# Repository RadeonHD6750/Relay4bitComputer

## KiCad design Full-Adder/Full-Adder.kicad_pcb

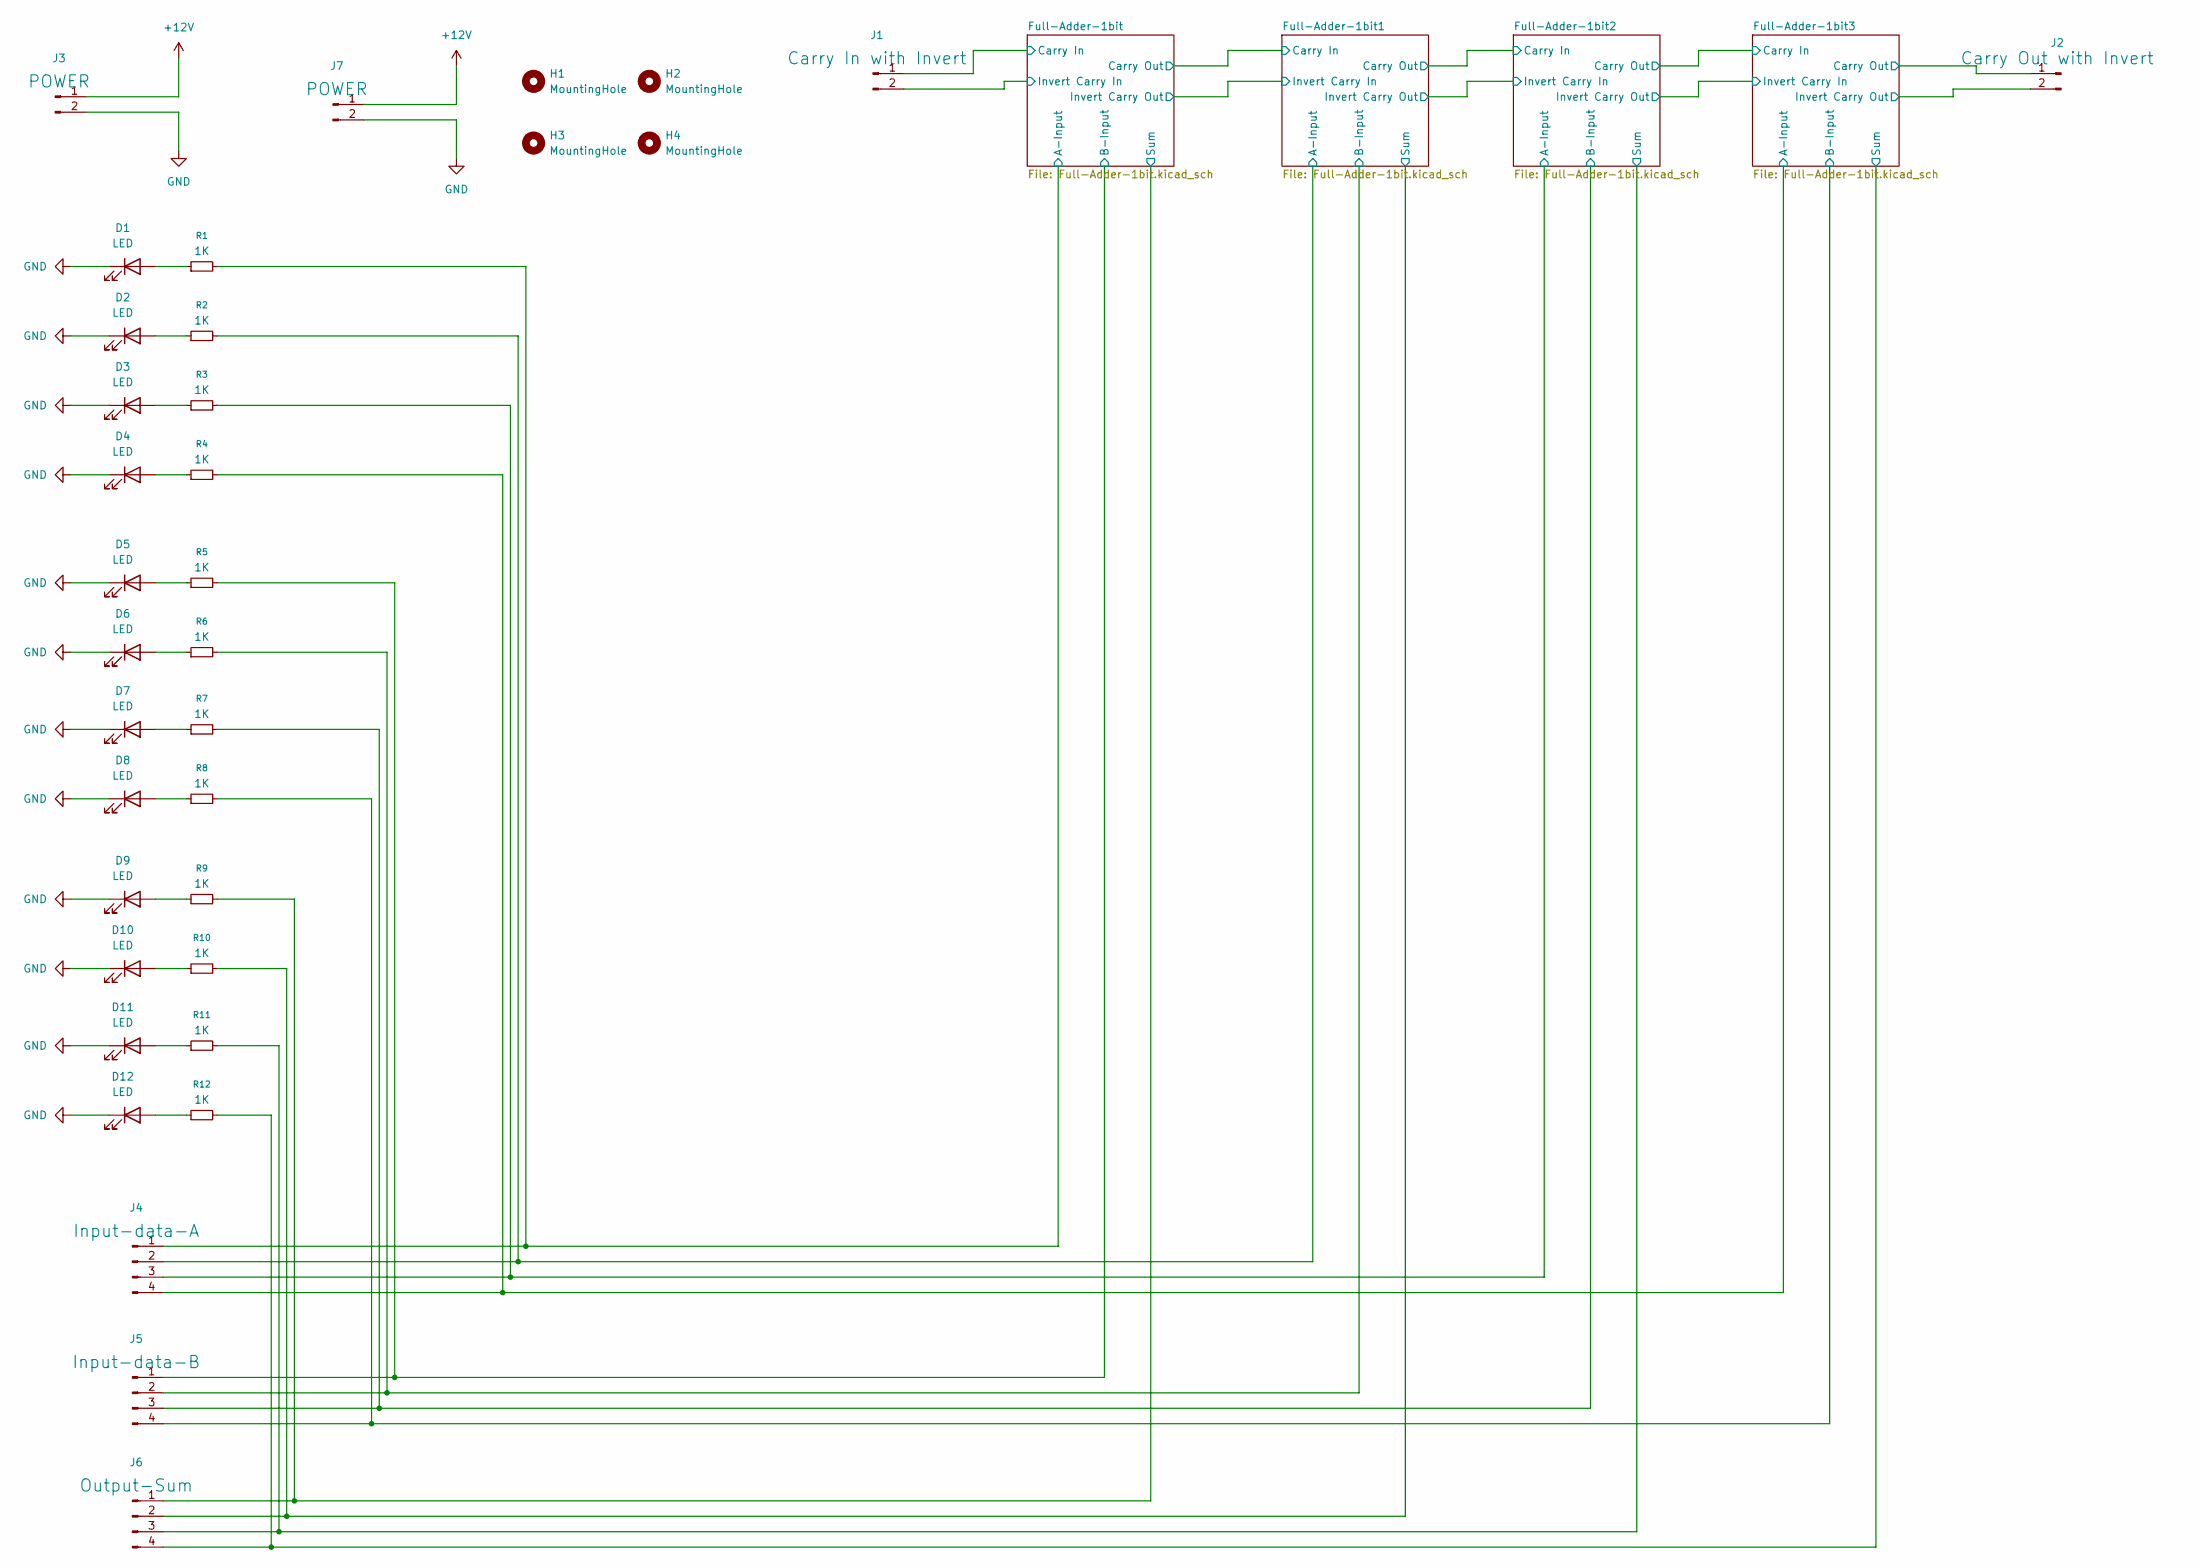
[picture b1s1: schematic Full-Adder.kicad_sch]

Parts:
D1, D2, D3, D4, D5, D6, D7, D8, D9, D10, D11, D12: LED; LED_D5.0mm
H1, H2, H3, H4: MountingHole; MountingHole_3.2mm_M3_Pad
J1: Carry In with Invert; PinHeader_1x02_P2.54mm_Vertical
J2: Carry Out with Invert; PinHeader_1x02_P2.54mm_Vertical
J3, J7: POWER; PinHeader_1x02_P2.54mm_Vertical
J4: Input-data-A; PinHeader_1x04_P2.54mm_Vertical
J5: Input-data-B; PinHeader_1x04_P2.54mm_Vertical
J6: Output-Sum; PinHeader_1x04_P2.54mm_Vertical
R1, R2, R3, R4, R5, R6, R7, R8, R9, R10, R11, R12: 1K; R_Axial_DIN0207_L6.3mm_D2.5mm_P10.16mm_Horizontal

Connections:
+12V: J3.1, J7.1; also elsewhere on the board
/Full-Adder-1bit1/A-Input: J4.2, R2.2; also elsewhere on the board
/Full-Adder-1bit1/B-Input: J5.2, R6.2; also elsewhere on the board
/Full-Adder-1bit1/Sum: J6.2, R10.2; also elsewhere on the board
/Full-Adder-1bit2/A-Input: J4.3, R3.2; also elsewhere on the board
/Full-Adder-1bit2/B-Input: J5.3, R7.2; also elsewhere on the board
/Full-Adder-1bit2/Sum: J6.3, R11.2; also elsewhere on the board
/Full-Adder-1bit3/A-Input: J4.4, R4.2; also elsewhere on the board
/Full-Adder-1bit3/B-Input: J5.4, R8.2; also elsewhere on the board
/Full-Adder-1bit3/Carry Out: J2.1; also elsewhere on the board
/Full-Adder-1bit3/Invert Carry Out: J2.2; also elsewhere on the board
/Full-Adder-1bit3/Sum: J6.4, R12.2; also elsewhere on the board
/Full-Adder-1bit/A-Input: J4.1, R1.2; also elsewhere on the board
/Full-Adder-1bit/B-Input: J5.1, R5.2; also elsewhere on the board
/Full-Adder-1bit/Carry In: J1.1; also elsewhere on the board
/Full-Adder-1bit/Invert Carry In: J1.2; also elsewhere on the board
/Full-Adder-1bit/Sum: J6.1, R9.2; also elsewhere on the board
GND: D1.1 (K), D2.1 (K), D3.1 (K), D4.1 (K), D5.1 (K), D6.1 (K), D7.1 (K), D8.1 (K), D9.1 (K), D10.1 (K), D11.1 (K), D12.1 (K), J3.2, J7.2; also elsewhere on the board
unnamed: D1.2 (A), R1.1
unnamed: D2.2 (A), R2.1
unnamed: D3.2 (A), R3.1
unnamed: D4.2 (A), R4.1
unnamed: D5.2 (A), R5.1
unnamed: D6.2 (A), R6.1
unnamed: D7.2 (A), R7.1
unnamed: D8.2 (A), R8.1
unnamed: D9.2 (A), R9.1
unnamed: D10.2 (A), R10.1
unnamed: D11.2 (A), R11.1
unnamed: D12.2 (A), R12.1

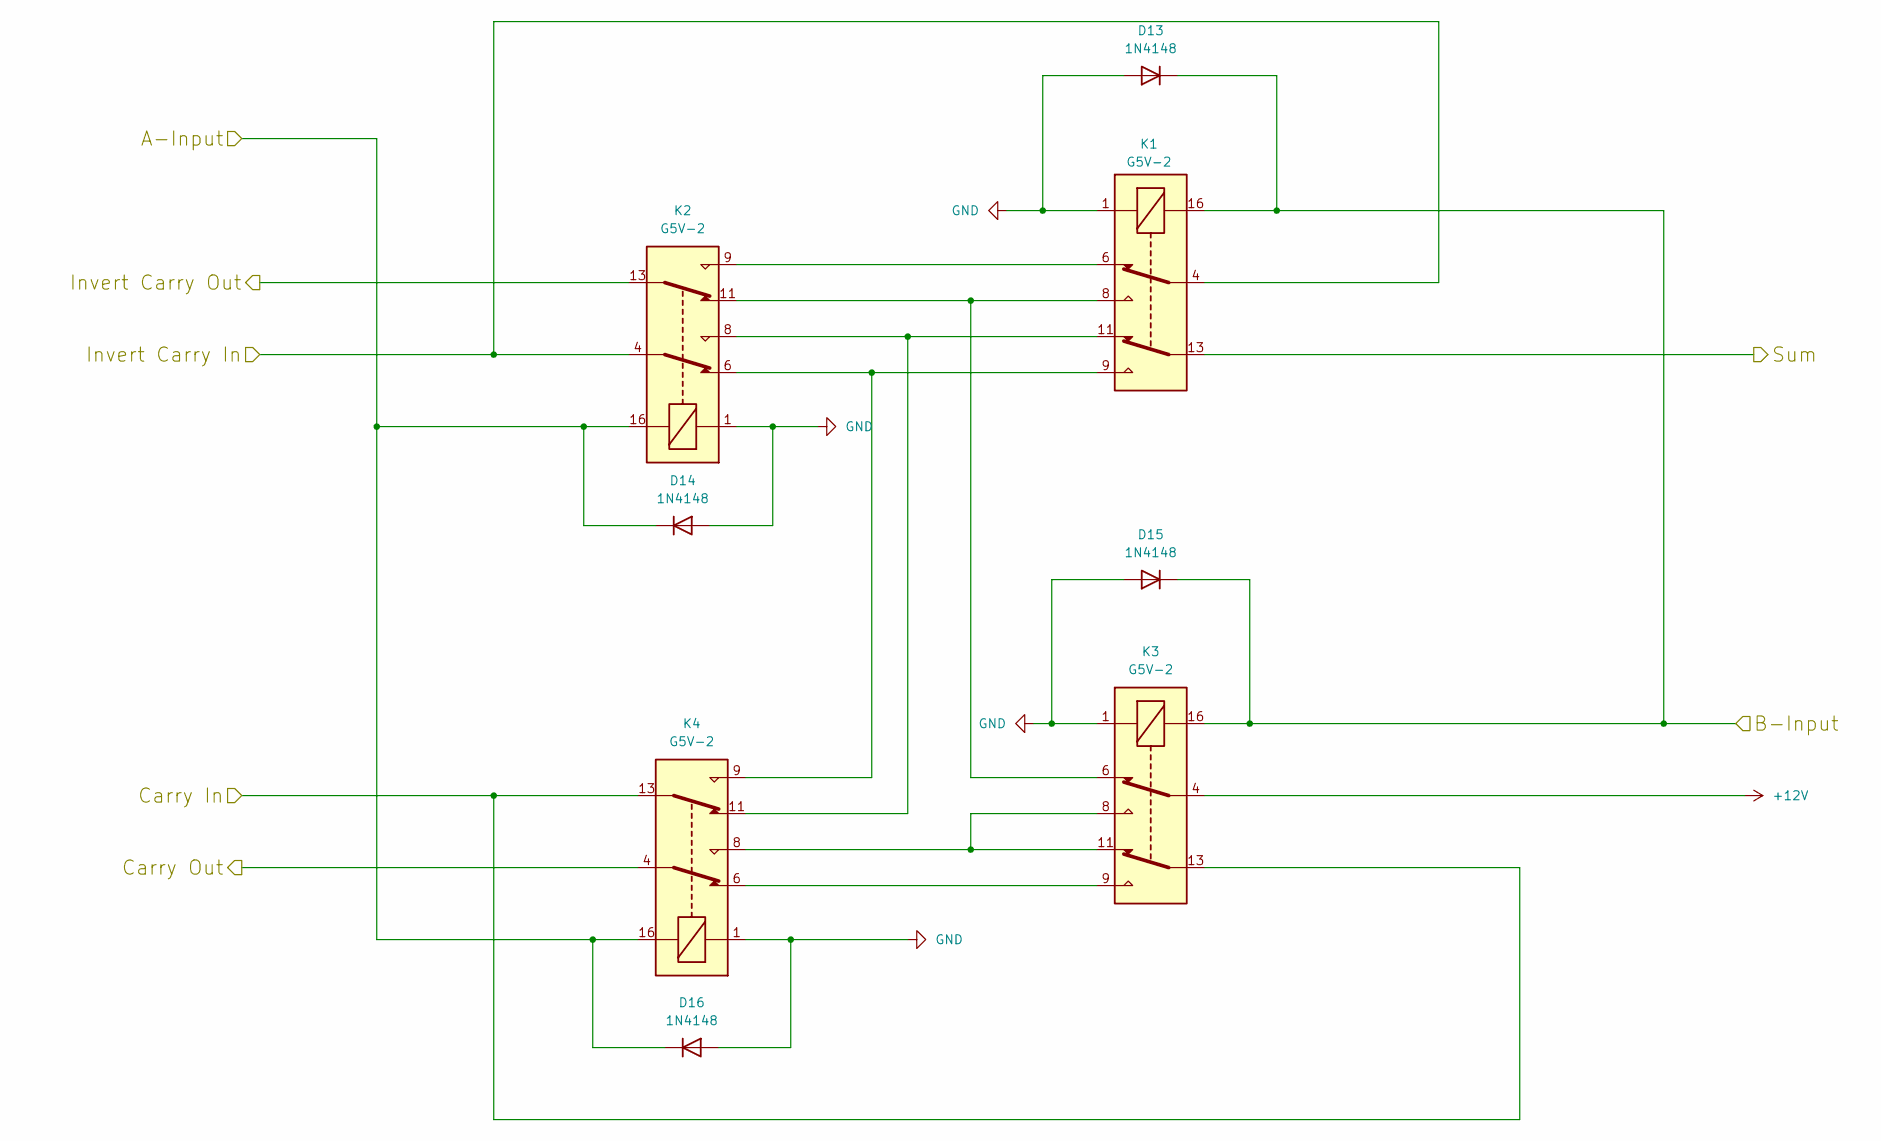
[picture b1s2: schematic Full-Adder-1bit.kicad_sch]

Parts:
D13, D14, D15, D16: 1N4148; D_DO-35_SOD27_P7.62mm_Horizontal
K1, K2, K3, K4: G5V-2; Relay_DPDT_Omron_G5V-2

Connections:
+12V: K3.4; also elsewhere on the board
/Full-Adder-1bit/A-Input: D14.1 (K), D16.1 (K), K2.16, K4.16; also elsewhere on the board
/Full-Adder-1bit/B-Input: D13.1 (K), D15.1 (K), K1.16, K3.16; also elsewhere on the board
/Full-Adder-1bit/Carry In: K3.13, K4.13; also elsewhere on the board
/Full-Adder-1bit/Carry Out: K4.4; also elsewhere on the board
/Full-Adder-1bit/Invert Carry In: K1.4, K2.4; also elsewhere on the board
/Full-Adder-1bit/Invert Carry Out: K2.13; also elsewhere on the board
/Full-Adder-1bit/Sum: K1.13; also elsewhere on the board
GND: D13.2 (A), D14.2 (A), D15.2 (A), D16.2 (A), K1.1, K2.1, K3.1, K4.1; also elsewhere on the board
unnamed: K1.6, K2.9
unnamed: K1.8, K2.11, K3.6
unnamed: K1.9, K2.6, K4.9
unnamed: K1.11, K2.8, K4.11
unnamed: K3.9, K4.6
unnamed: K3.8, K3.11, K4.8

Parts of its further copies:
D17, D18, D19, D20, D21, D22, D23, D24, D25, D26, D27, D28: 1N4148; D_DO-35_SOD27_P7.62mm_Horizontal
K5, K6, K7, K8, K9, K10, K11, K12, K13, K14, K15, K16: G5V-2; Relay_DPDT_Omron_G5V-2

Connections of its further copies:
+12V: K7.4, K11.4, K15.4; also elsewhere on the board
/Full-Adder-1bit1/A-Input: D18.1 (K), D20.1 (K), K6.16, K8.16; also elsewhere on the board
/Full-Adder-1bit1/B-Input: D17.1 (K), D19.1 (K), K5.16, K7.16; also elsewhere on the board
/Full-Adder-1bit1/Carry Out: K8.4, K11.13, K12.13
/Full-Adder-1bit1/Invert Carry Out: K6.13, K9.4, K10.4
/Full-Adder-1bit1/Sum: K5.13; also elsewhere on the board
/Full-Adder-1bit2/A-Input: D22.1 (K), D24.1 (K), K10.16, K12.16; also elsewhere on the board
/Full-Adder-1bit2/B-Input: D21.1 (K), D23.1 (K), K9.16, K11.16; also elsewhere on the board
/Full-Adder-1bit2/Carry Out: K12.4, K15.13, K16.13
/Full-Adder-1bit2/Invert Carry Out: K10.13, K13.4, K14.4
/Full-Adder-1bit2/Sum: K9.13; also elsewhere on the board
/Full-Adder-1bit3/A-Input: D26.1 (K), D28.1 (K), K14.16, K16.16; also elsewhere on the board
/Full-Adder-1bit3/B-Input: D25.1 (K), D27.1 (K), K13.16, K15.16; also elsewhere on the board
/Full-Adder-1bit3/Carry Out: K16.4; also elsewhere on the board
/Full-Adder-1bit3/Invert Carry Out: K14.13; also elsewhere on the board
/Full-Adder-1bit3/Sum: K13.13; also elsewhere on the board
/Full-Adder-1bit/Carry Out: K7.13, K8.13; also elsewhere on the board
/Full-Adder-1bit/Invert Carry Out: K5.4, K6.4; also elsewhere on the board
GND: D17.2 (A), D18.2 (A), D19.2 (A), D20.2 (A), D21.2 (A), D22.2 (A), D23.2 (A), D24.2 (A), D25.2 (A), D26.2 (A), D27.2 (A), D28.2 (A), K5.1, K6.1, K7.1, K8.1, K9.1, K10.1, K11.1, K12.1, K13.1, K14.1, K15.1, K16.1; also elsewhere on the board
unnamed: K5.6, K6.9
unnamed: K5.8, K6.11, K7.6
unnamed: K5.9, K6.6, K8.9
unnamed: K5.11, K6.8, K8.11
unnamed: K7.9, K8.6
unnamed: K7.8, K7.11, K8.8
unnamed: K9.9, K10.6, K12.9
unnamed: K9.11, K10.8, K12.11
unnamed: K9.6, K10.9
unnamed: K9.8, K10.11, K11.6
unnamed: K11.9, K12.6
unnamed: K11.8, K11.11, K12.8
unnamed: K13.6, K14.9
unnamed: K13.8, K14.11, K15.6
unnamed: K13.9, K14.6, K16.9
unnamed: K13.11, K14.8, K16.11
unnamed: K15.9, K16.6
unnamed: K15.8, K15.11, K16.8

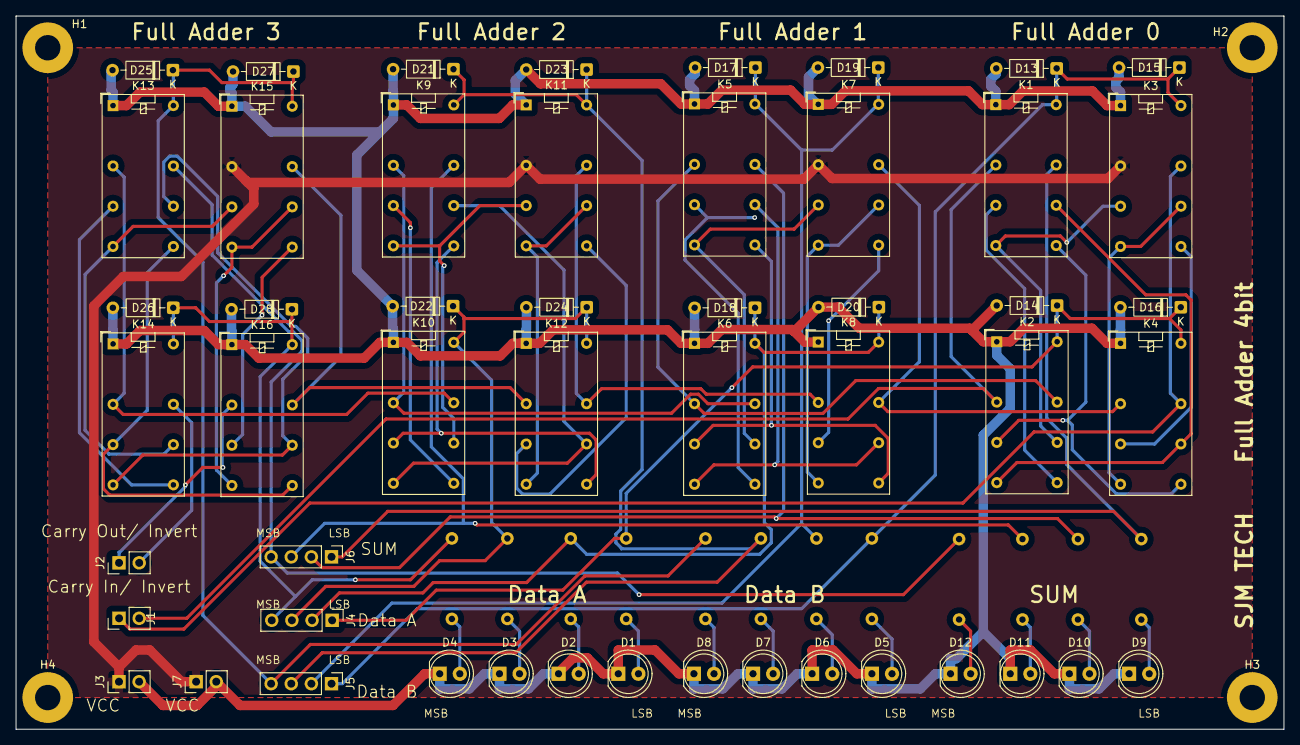
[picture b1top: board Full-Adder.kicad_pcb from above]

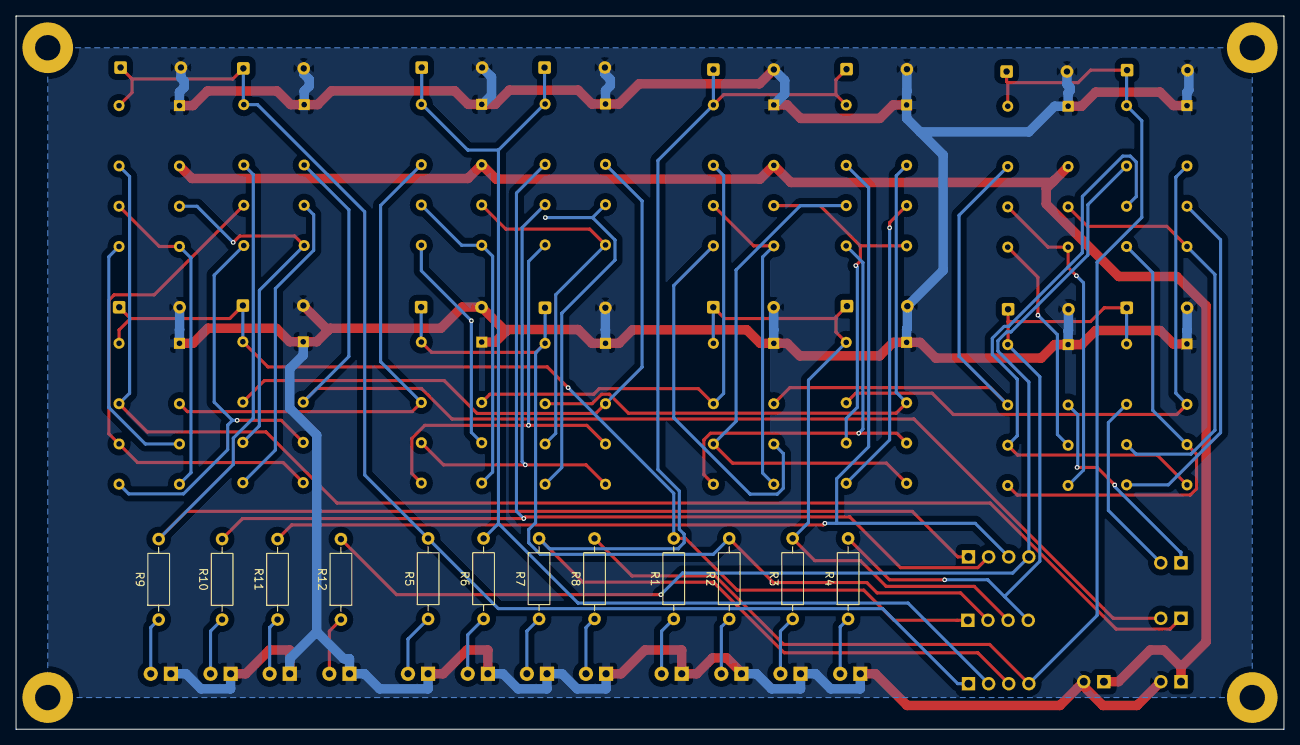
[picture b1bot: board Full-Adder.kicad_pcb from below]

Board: 2 copper layers, 160.0 x 90.0 mm, 67 parts (12 on the bottom side), 60 nets.

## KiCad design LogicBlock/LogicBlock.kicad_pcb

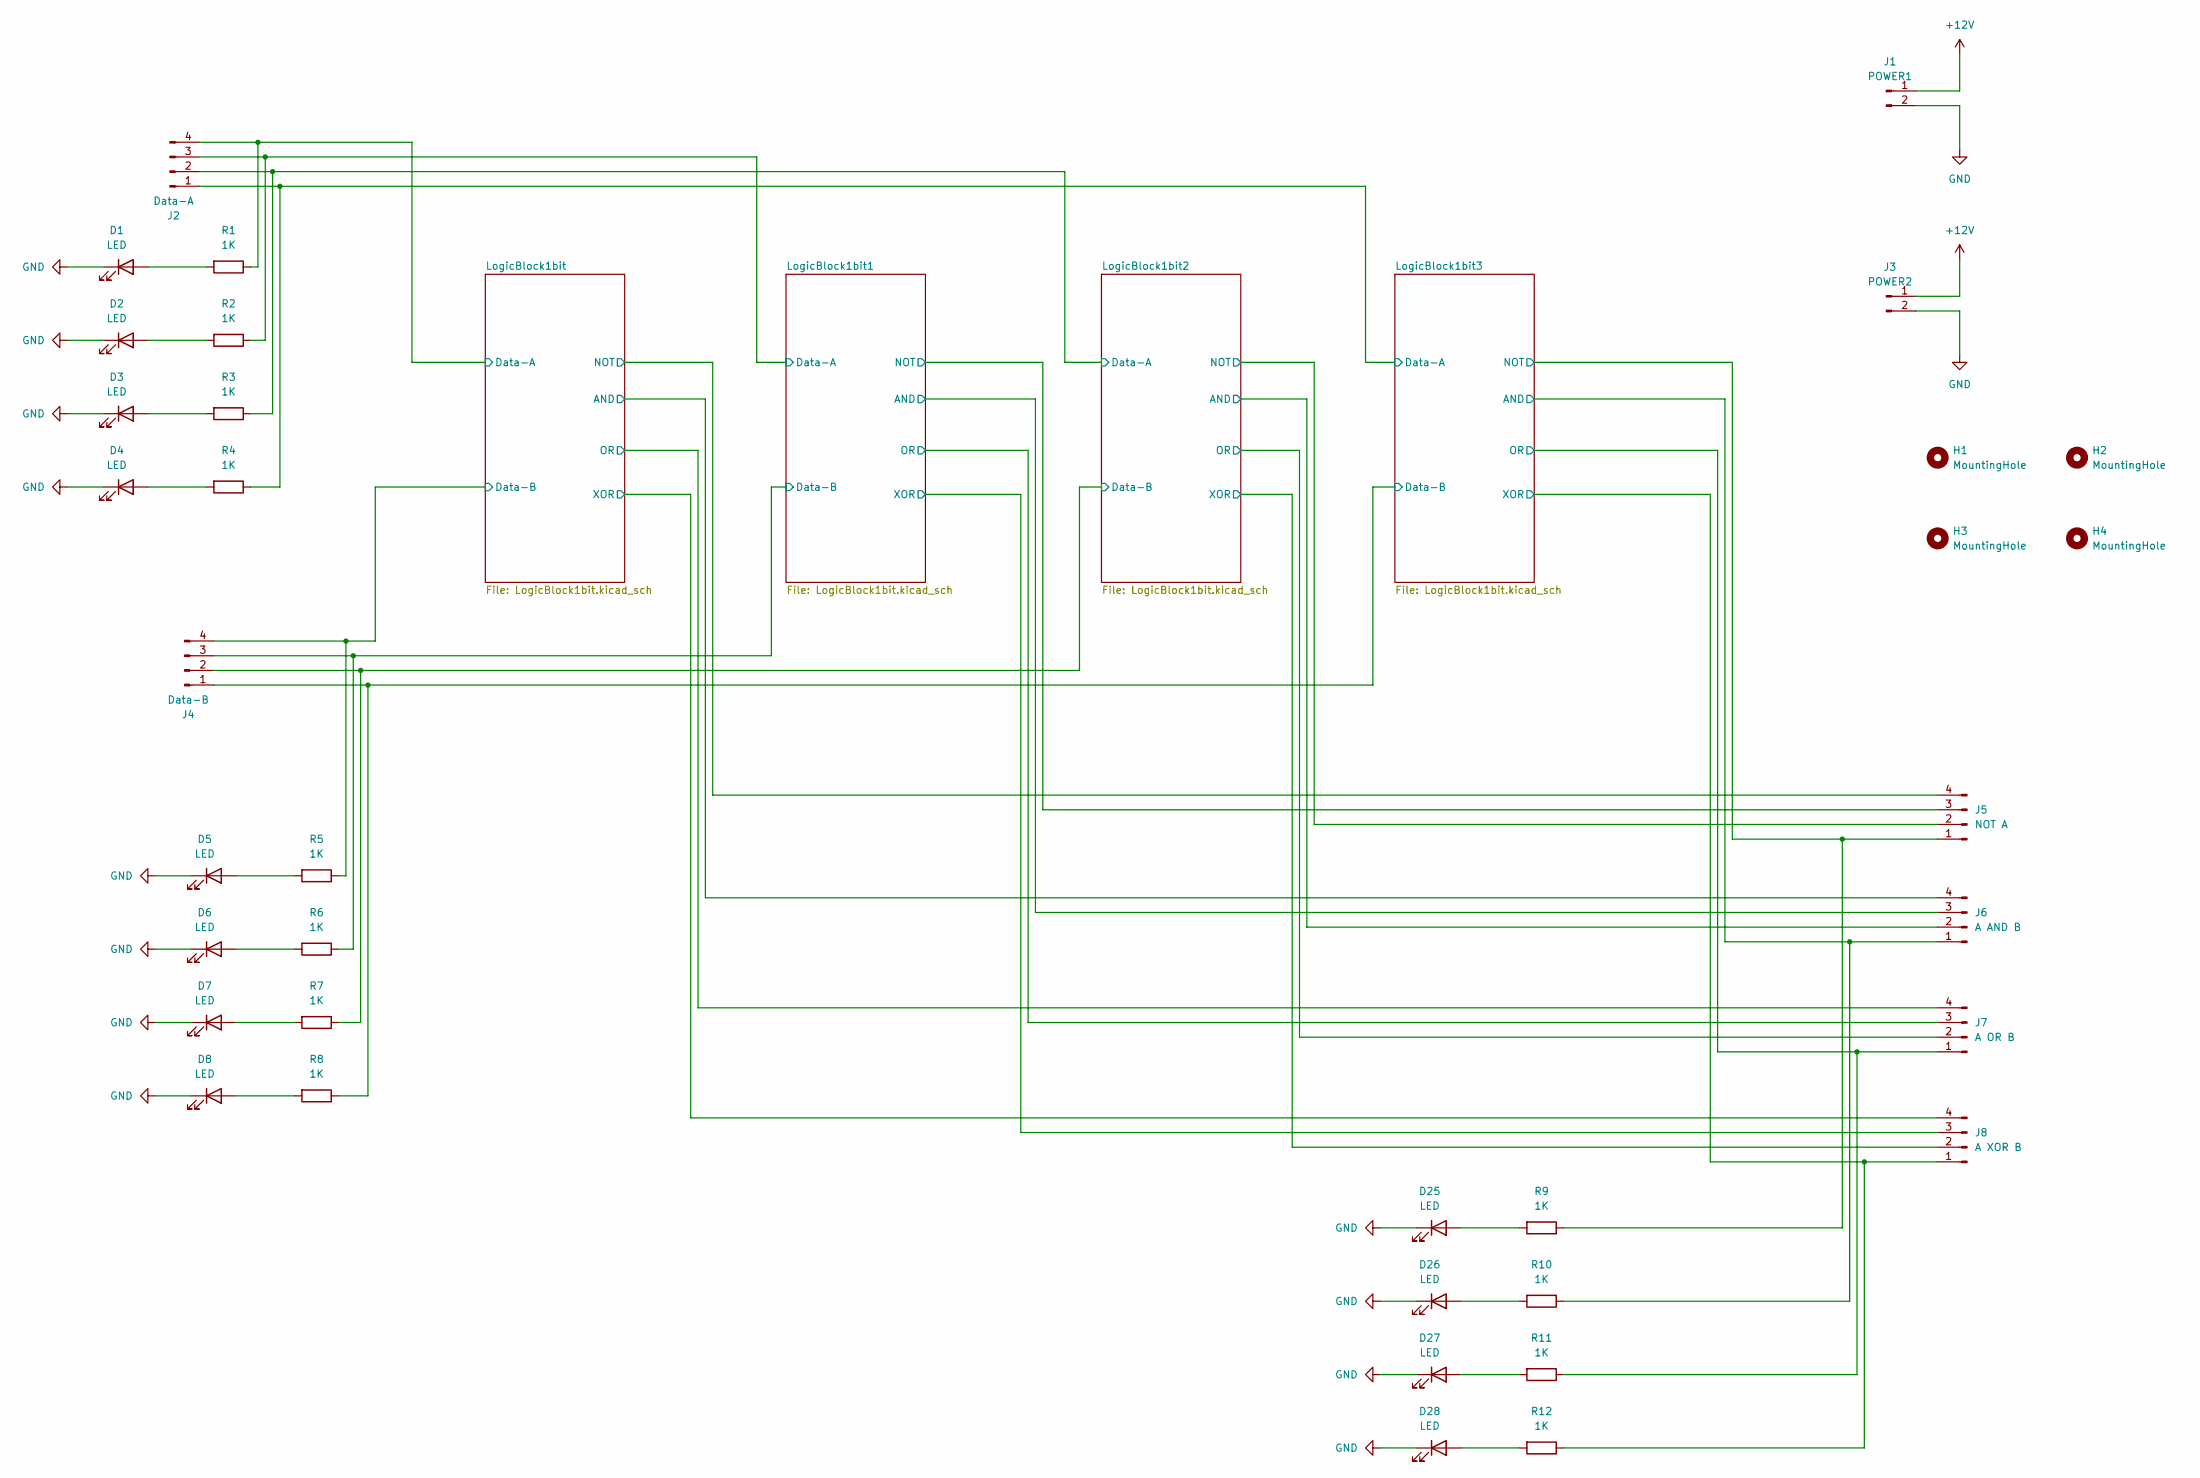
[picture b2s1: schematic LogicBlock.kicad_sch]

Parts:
D1, D2, D3, D4, D5, D6, D7, D8, D25, D26, D27, D28: LED; LED_D5.0mm
H1, H2, H3, H4: MountingHole; MountingHole_3.2mm_M3
J1: POWER1; PinHeader_1x02_P2.54mm_Vertical
J2: Data-A; PinHeader_1x04_P2.54mm_Vertical
J3: POWER2; PinHeader_1x02_P2.54mm_Vertical
J4: Data-B; PinHeader_1x04_P2.54mm_Vertical
J5: NOT A; PinHeader_1x04_P2.54mm_Vertical
J6: A AND B; PinHeader_1x04_P2.54mm_Vertical
J7: A OR B; PinHeader_1x04_P2.54mm_Vertical
J8: A XOR B; PinHeader_1x04_P2.54mm_Vertical
R1, R2, R3, R4, R5, R6, R7, R8, R9, R10, R11, R12: 1K; R_Axial_DIN0207_L6.3mm_D2.5mm_P10.16mm_Horizontal

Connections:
+12V: J1.1, J3.1; also elsewhere on the board
/LogicBlock1bit1/AND: J6.3; also elsewhere on the board
/LogicBlock1bit1/Data-A: J2.3, R2.1; also elsewhere on the board
/LogicBlock1bit1/Data-B: J4.3, R6.1; also elsewhere on the board
/LogicBlock1bit1/NOT: J5.3; also elsewhere on the board
/LogicBlock1bit1/OR: J7.3; also elsewhere on the board
/LogicBlock1bit1/XOR: J8.3; also elsewhere on the board
/LogicBlock1bit2/AND: J6.2; also elsewhere on the board
/LogicBlock1bit2/Data-A: J2.2, R3.1; also elsewhere on the board
/LogicBlock1bit2/Data-B: J4.2, R7.1; also elsewhere on the board
/LogicBlock1bit2/NOT: J5.2; also elsewhere on the board
/LogicBlock1bit2/OR: J7.2; also elsewhere on the board
/LogicBlock1bit2/XOR: J8.2; also elsewhere on the board
/LogicBlock1bit3/AND: J6.1, R10.1; also elsewhere on the board
/LogicBlock1bit3/Data-A: J2.1, R4.1; also elsewhere on the board
/LogicBlock1bit3/Data-B: J4.1, R8.1; also elsewhere on the board
/LogicBlock1bit3/NOT: J5.1, R9.1; also elsewhere on the board
/LogicBlock1bit3/OR: J7.1, R11.1; also elsewhere on the board
/LogicBlock1bit3/XOR: J8.1, R12.1; also elsewhere on the board
/LogicBlock1bit/AND: J6.4; also elsewhere on the board
/LogicBlock1bit/Data-A: J2.4, R1.1; also elsewhere on the board
/LogicBlock1bit/Data-B: J4.4, R5.1; also elsewhere on the board
/LogicBlock1bit/NOT: J5.4; also elsewhere on the board
/LogicBlock1bit/OR: J7.4; also elsewhere on the board
/LogicBlock1bit/XOR: J8.4; also elsewhere on the board
GND: D1.1 (K), D2.1 (K), D3.1 (K), D4.1 (K), D5.1 (K), D6.1 (K), D7.1 (K), D8.1 (K), D25.1 (K), D26.1 (K), D27.1 (K), D28.1 (K), J1.2, J3.2; also elsewhere on the board
unnamed: D1.2 (A), R1.2
unnamed: D2.2 (A), R2.2
unnamed: D3.2 (A), R3.2
unnamed: D4.2 (A), R4.2
unnamed: D5.2 (A), R5.2
unnamed: D6.2 (A), R6.2
unnamed: D7.2 (A), R7.2
unnamed: D8.2 (A), R8.2
unnamed: D25.2 (A), R9.2
unnamed: D26.2 (A), R10.2
unnamed: D27.2 (A), R11.2
unnamed: D28.2 (A), R12.2

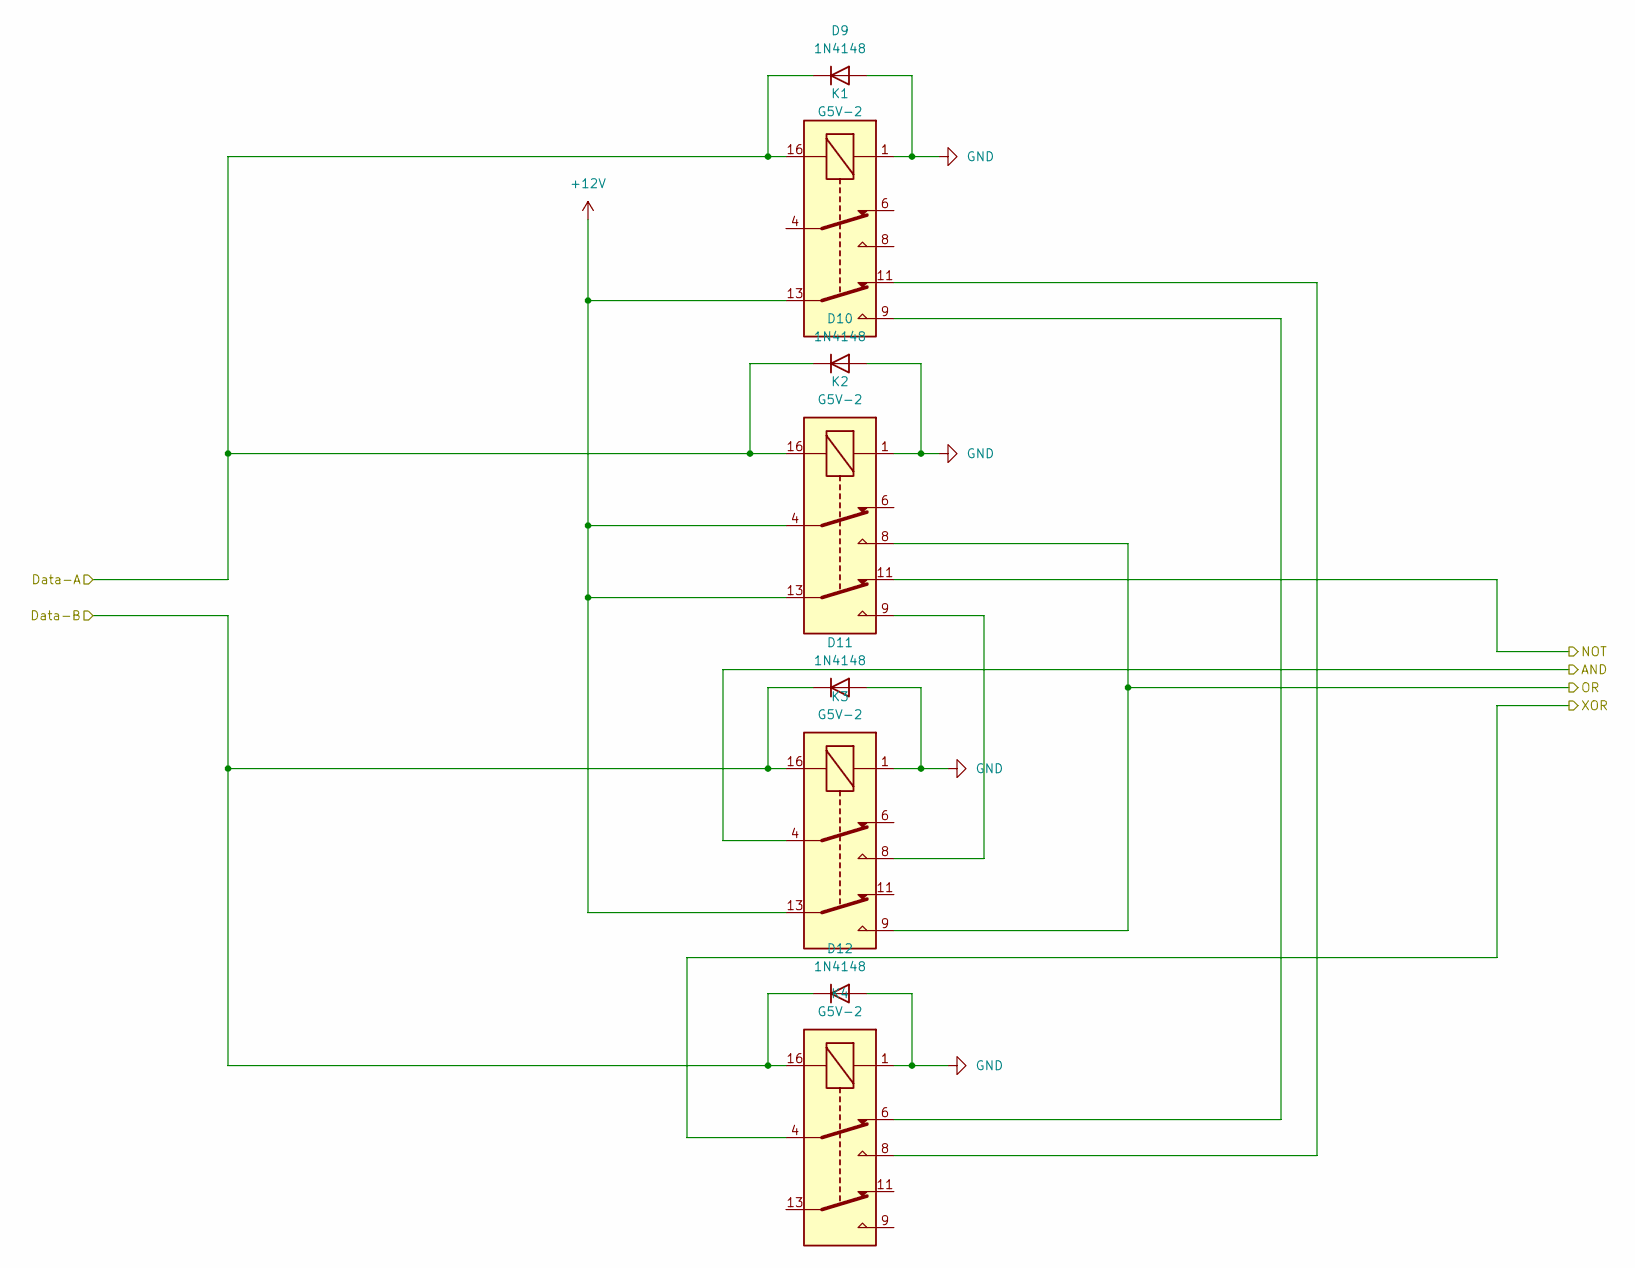
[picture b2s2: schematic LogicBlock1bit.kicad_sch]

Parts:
D9, D10, D11, D12: 1N4148; D_DO-35_SOD27_P7.62mm_Horizontal
K1, K2, K3, K4: G5V-2; Relay_DPDT_Omron_G5V-2

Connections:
+12V: K1.13, K2.4, K2.13, K3.13; also elsewhere on the board
/LogicBlock1bit/AND: K3.4; also elsewhere on the board
/LogicBlock1bit/Data-A: D9.1 (K), D10.1 (K), K1.16, K2.16; also elsewhere on the board
/LogicBlock1bit/Data-B: D11.1 (K), D12.1 (K), K3.16, K4.16; also elsewhere on the board
/LogicBlock1bit/NOT: K2.11; also elsewhere on the board
/LogicBlock1bit/OR: K2.8, K3.9; also elsewhere on the board
/LogicBlock1bit/XOR: K4.4; also elsewhere on the board
GND: D9.2 (A), D10.2 (A), D11.2 (A), D12.2 (A), K1.1, K2.1, K3.1, K4.1; also elsewhere on the board
unnamed: K1.9, K4.6
unnamed: K1.11, K4.8
unnamed: K2.9, K3.8

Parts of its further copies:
D13, D14, D15, D16, D17, D18, D19, D20, D21, D22, D23, D24: 1N4148; D_DO-35_SOD27_P7.62mm_Horizontal
K5, K6, K7, K8, K9, K10, K11, K12, K13, K14, K15, K16: G5V-2; Relay_DPDT_Omron_G5V-2

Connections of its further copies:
+12V: K5.13, K6.4, K6.13, K7.13, K9.13, K10.4, K10.13, K11.13, K13.13, K14.4, K14.13, K15.13; also elsewhere on the board
/LogicBlock1bit1/AND: K7.4; also elsewhere on the board
/LogicBlock1bit1/Data-A: D13.1 (K), D14.1 (K), K5.16, K6.16; also elsewhere on the board
/LogicBlock1bit1/Data-B: D15.1 (K), D16.1 (K), K7.16, K8.16; also elsewhere on the board
/LogicBlock1bit1/NOT: K6.11; also elsewhere on the board
/LogicBlock1bit1/OR: K6.8, K7.9; also elsewhere on the board
/LogicBlock1bit1/XOR: K8.4; also elsewhere on the board
/LogicBlock1bit2/AND: K11.4; also elsewhere on the board
/LogicBlock1bit2/Data-A: D17.1 (K), D18.1 (K), K9.16, K10.16; also elsewhere on the board
/LogicBlock1bit2/Data-B: D19.1 (K), D20.1 (K), K11.16, K12.16; also elsewhere on the board
/LogicBlock1bit2/NOT: K10.11; also elsewhere on the board
/LogicBlock1bit2/OR: K10.8, K11.9; also elsewhere on the board
/LogicBlock1bit2/XOR: K12.4; also elsewhere on the board
/LogicBlock1bit3/AND: K15.4; also elsewhere on the board
/LogicBlock1bit3/Data-A: D21.1 (K), D22.1 (K), K13.16, K14.16; also elsewhere on the board
/LogicBlock1bit3/Data-B: D23.1 (K), D24.1 (K), K15.16, K16.16; also elsewhere on the board
/LogicBlock1bit3/NOT: K14.11; also elsewhere on the board
/LogicBlock1bit3/OR: K14.8, K15.9; also elsewhere on the board
/LogicBlock1bit3/XOR: K16.4; also elsewhere on the board
GND: D13.2 (A), D14.2 (A), D15.2 (A), D16.2 (A), D17.2 (A), D18.2 (A), D19.2 (A), D20.2 (A), D21.2 (A), D22.2 (A), D23.2 (A), D24.2 (A), K5.1, K6.1, K7.1, K8.1, K9.1, K10.1, K11.1, K12.1, K13.1, K14.1, K15.1, K16.1; also elsewhere on the board
unnamed: K5.9, K8.6
unnamed: K5.11, K8.8
unnamed: K6.9, K7.8
unnamed: K10.9, K11.8
unnamed: K9.9, K12.6
unnamed: K9.11, K12.8
unnamed: K13.9, K16.6
unnamed: K13.11, K16.8
unnamed: K14.9, K15.8

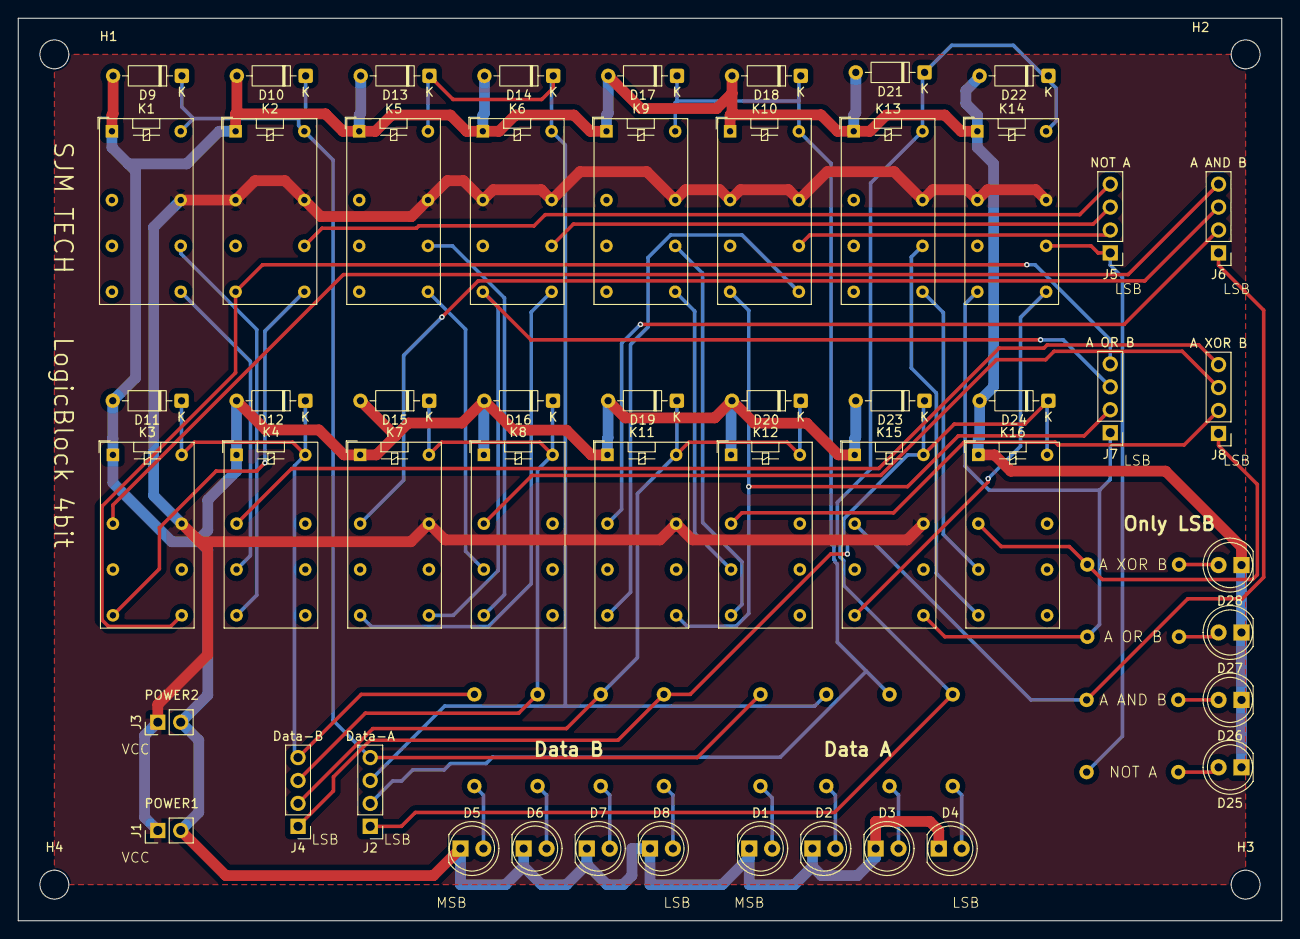
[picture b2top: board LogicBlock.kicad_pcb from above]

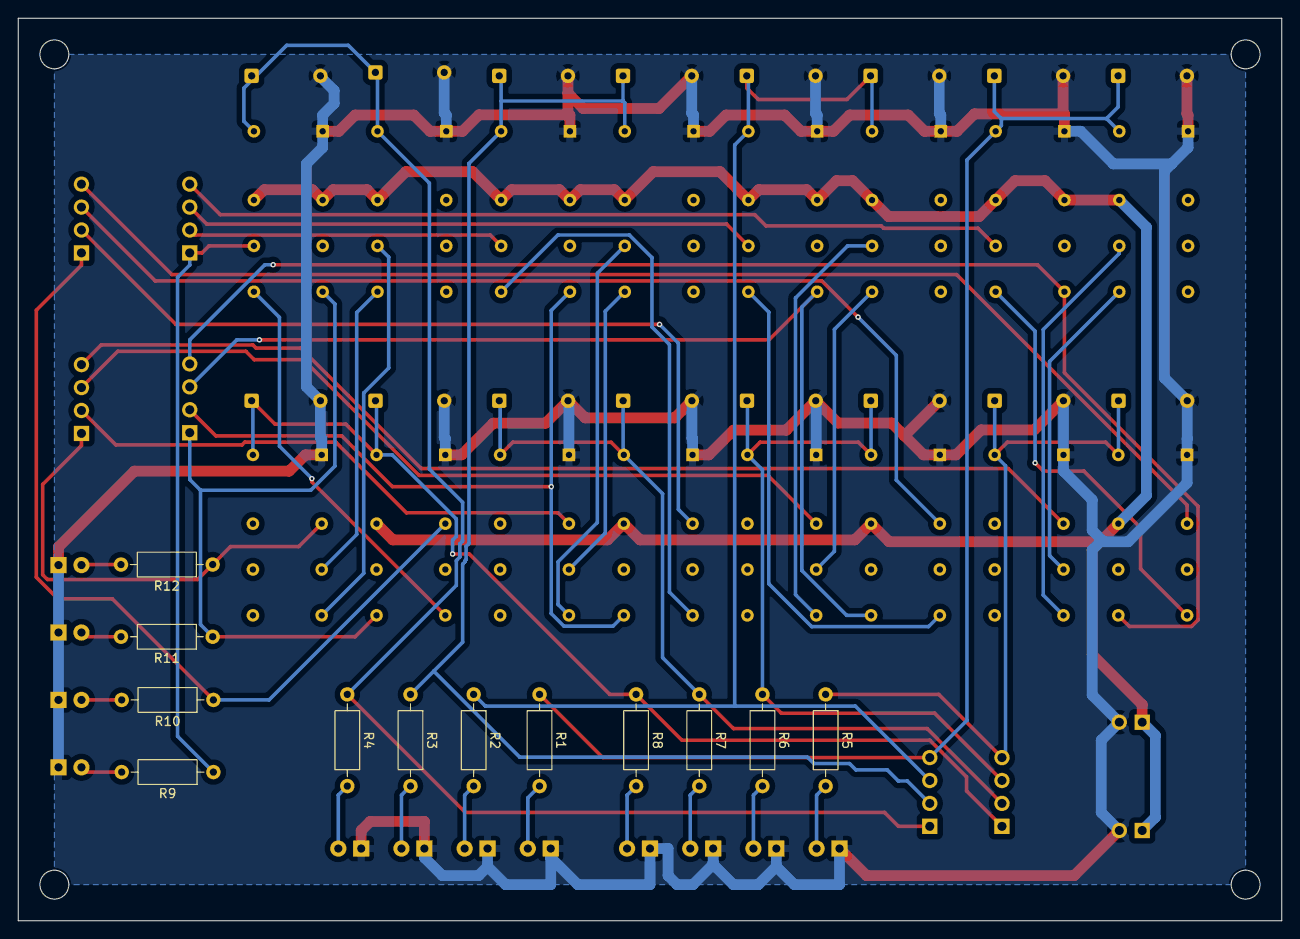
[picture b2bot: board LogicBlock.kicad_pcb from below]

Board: 2 copper layers, 140.0 x 100.0 mm, 68 parts (12 on the bottom side), 50 nets.
